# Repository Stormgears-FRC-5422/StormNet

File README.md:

# StormNet
Electrical schematics and other files related to the StormNet sensor board

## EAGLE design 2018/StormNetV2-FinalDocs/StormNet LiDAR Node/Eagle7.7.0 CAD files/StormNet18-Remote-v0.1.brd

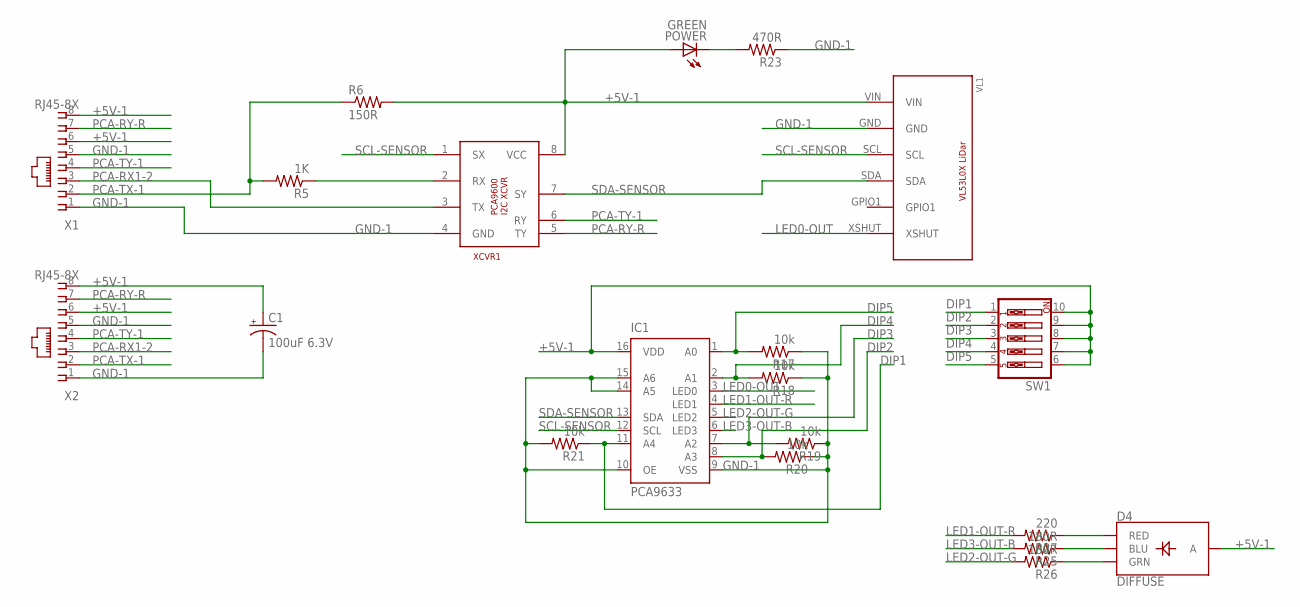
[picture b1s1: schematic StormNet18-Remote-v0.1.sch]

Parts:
C1: 100uF 6.3V; CT3528
D4: DIFFUSE; LED-RGB-THRU
IC1: PCA9633; SO16
POWER: GREEN; CHIPLED_1206
R5: 1K; R0603
R6: 150R; R0603
R17, R18, R19, R20, R21: 10k; R0603
R23: 470R; R0603
R25, R26: 180R; R0603
R27: 220; R0603
SW1: SW_DIP-5; EDG-05
VL1: VL53L0X-GREEN
X1, X2: RJ45-8X; RJ45-NO-SHIELD
XCVR1: PCA9600DSO8; SO08

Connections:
+5V-1: C1.+, D4.2 (A), IC1.16 (VDD), POWER.A, R6.2, SW1.6, SW1.7, SW1.8, SW1.9, SW1.10, VL1.VIN, X1.6, X1.8, X2.6, X2.8, XCVR1.8 (VCC)
BLUE: D4.4 (BLU), R25.1
DIP1: IC1.11 (A4), R21.1, SW1.1
DIP2: IC1.8 (A3), R20.2, SW1.2
DIP3: IC1.7 (A2), R19.2, SW1.3
DIP4: IC1.2 (A1), R18.2, SW1.4
DIP5: IC1.1 (A0), R17.2, SW1.5
GND-1: C1.-, IC1.9 (VSS), IC1.10 (OE), IC1.14 (A5), IC1.15 (A6), R17.1, R18.1, R19.1, R20.1, R21.2, R23.1, VL1.GND, X1.1, X1.5, X2.1, X2.5, XCVR1.4 (GND)
GREEN: D4.3 (GRN), R26.1
LED0-OUT: IC1.3 (LED0), VL1.XSHUT
LED1-OUT-R: IC1.4 (LED1), R27.2
LED2-OUT-G: IC1.5 (LED2), R26.2
LED3-OUT-B: IC1.6 (LED3), R25.2
unnamed: R5.1, XCVR1.2 (RX)
unnamed: POWER.C, R23.2
PCA-RX1-2: X1.3, X2.3, XCVR1.3 (TX)
PCA-RY-R: X1.7, X2.7, XCVR1.5 (TY)
PCA-TX-1: R5.2, R6.1, X1.2, X2.2
PCA-TY-1: X1.4, X2.4, XCVR1.6 (RY)
RED: D4.1 (RED), R27.1
SCL-SENSOR: IC1.12 (SCL), VL1.SCL, XCVR1.1 (SX)
SDA-SENSOR: IC1.13 (SDA), VL1.SDA, XCVR1.7 (SY)

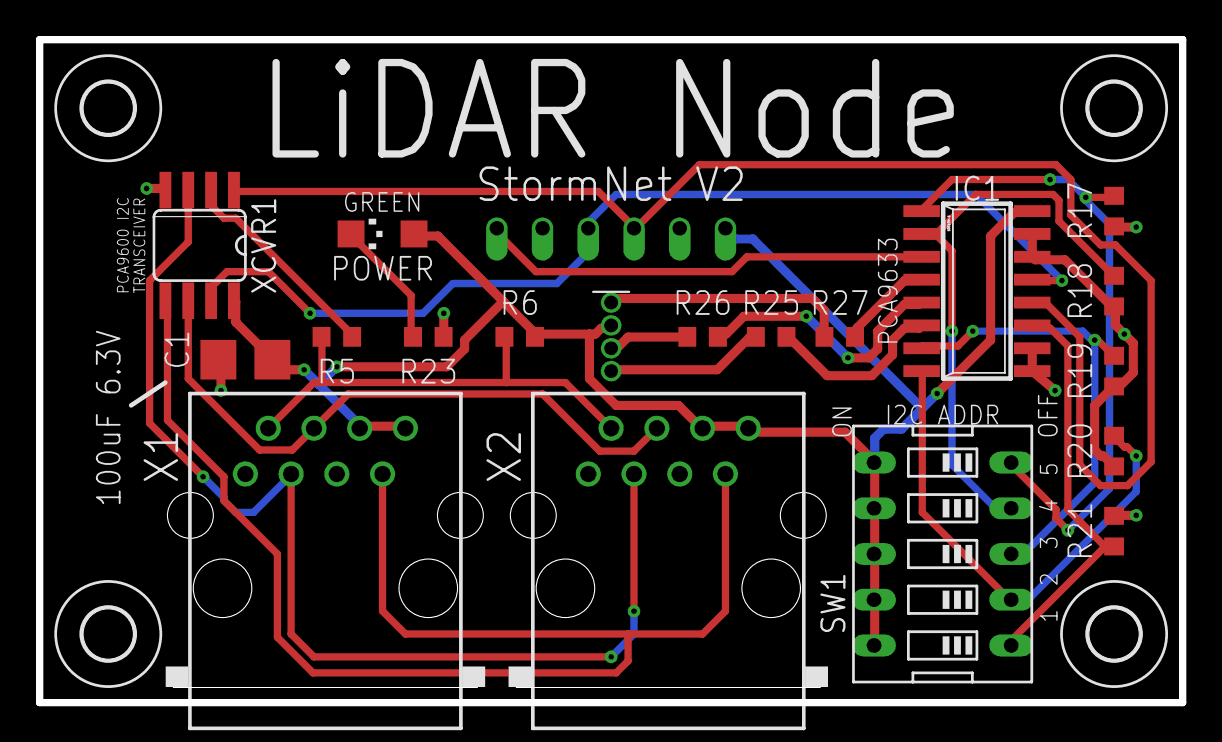
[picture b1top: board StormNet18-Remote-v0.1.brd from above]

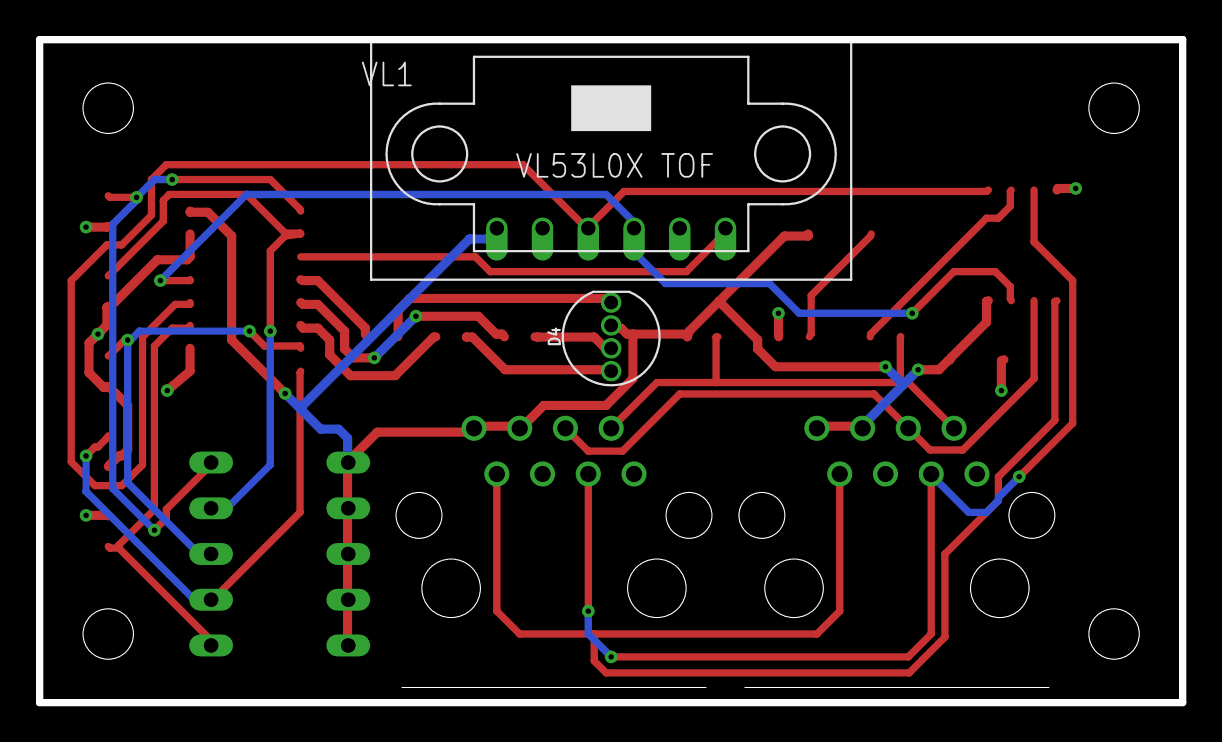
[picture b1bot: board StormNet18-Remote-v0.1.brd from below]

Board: 2 copper layers, 63.5 x 36.8 mm, 24 parts (2 on the bottom side), 22 nets.

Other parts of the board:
U$5, U$6, U$7, U$8: 2,8

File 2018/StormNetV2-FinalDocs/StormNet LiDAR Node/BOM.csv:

"Part","Value","Device","Package","DescriptionMF","MPN","OC_FARNELL","OC_NEWARK","PROD_ID","VALUE",
"C1","100uF 6.3V","CPOL-USCT3528","CT3528","POLARIZED CAPACITOR, American symbol","","","","","",
"D4","DIFFUSE","LED-RGB-CADIFFUSE","LED-RGB-THRU","LED-RGB Diffused Common Anode","","","","","DIO-10632",
"IC1","PCA9633","PCA9633","SO16","4-bit I2C-bus and SMBus low power I/O port with LED drivers","","","","","",
"POWER","GREEN","LEDCHIPLED_1206","CHIPLED_1206","LED","","","","","",
"R5","1K","R-US_R0603","R0603","RESISTOR, American symbol","","","","","",
"R6","150R","R-US_R0603","R0603","RESISTOR, American symbol","","","","","",
"R17","10k","R-US_R0603","R0603","RESISTOR, American symbol","","","","","",
"R18","10k","R-US_R0603","R0603","RESISTOR, American symbol","","","","","",
"R19","10k","R-US_R0603","R0603","RESISTOR, American symbol","","","","","",
"R20","10k","R-US_R0603","R0603","RESISTOR, American symbol","","","","","",
"R21","10k","R-US_R0603","R0603","RESISTOR, American symbol","","","","","",
"R23","470R","R-US_R0603","R0603","RESISTOR, American symbol","","","","","",
"R25","180R","R-US_R0603","R0603","RESISTOR, American symbol","","","","","",
"R26","180R","R-US_R0603","R0603","RESISTOR, American symbol","","","","","",
"R27","220","R-US_R0603","R0603","RESISTOR, American symbol","","","","","",
"SW1","","SW_DIP-5","EDG-05","DIP SWITCH","","","","","",
"VL1","VL53L0X-GREEN","VL53L0X-GREEN","VL53L0X-GREEN","","","","","","",
"X1","RJ45-8X","RJ45-8X","RJ45-NO-SHIELD","CORCOM Modular RJ Jacks No Shield","","RJ45-8X","unknown","16R6101","",
"X2","RJ45-8X","RJ45-8X","RJ45-NO-SHIELD","CORCOM Modular RJ Jacks No Shield","","RJ45-8X","unknown","16R6101","",
"XCVR1","PCA9600DSO8","PCA9600DSO8","SO08","NXP PCA9600 I2C long distance driver","","","","","",

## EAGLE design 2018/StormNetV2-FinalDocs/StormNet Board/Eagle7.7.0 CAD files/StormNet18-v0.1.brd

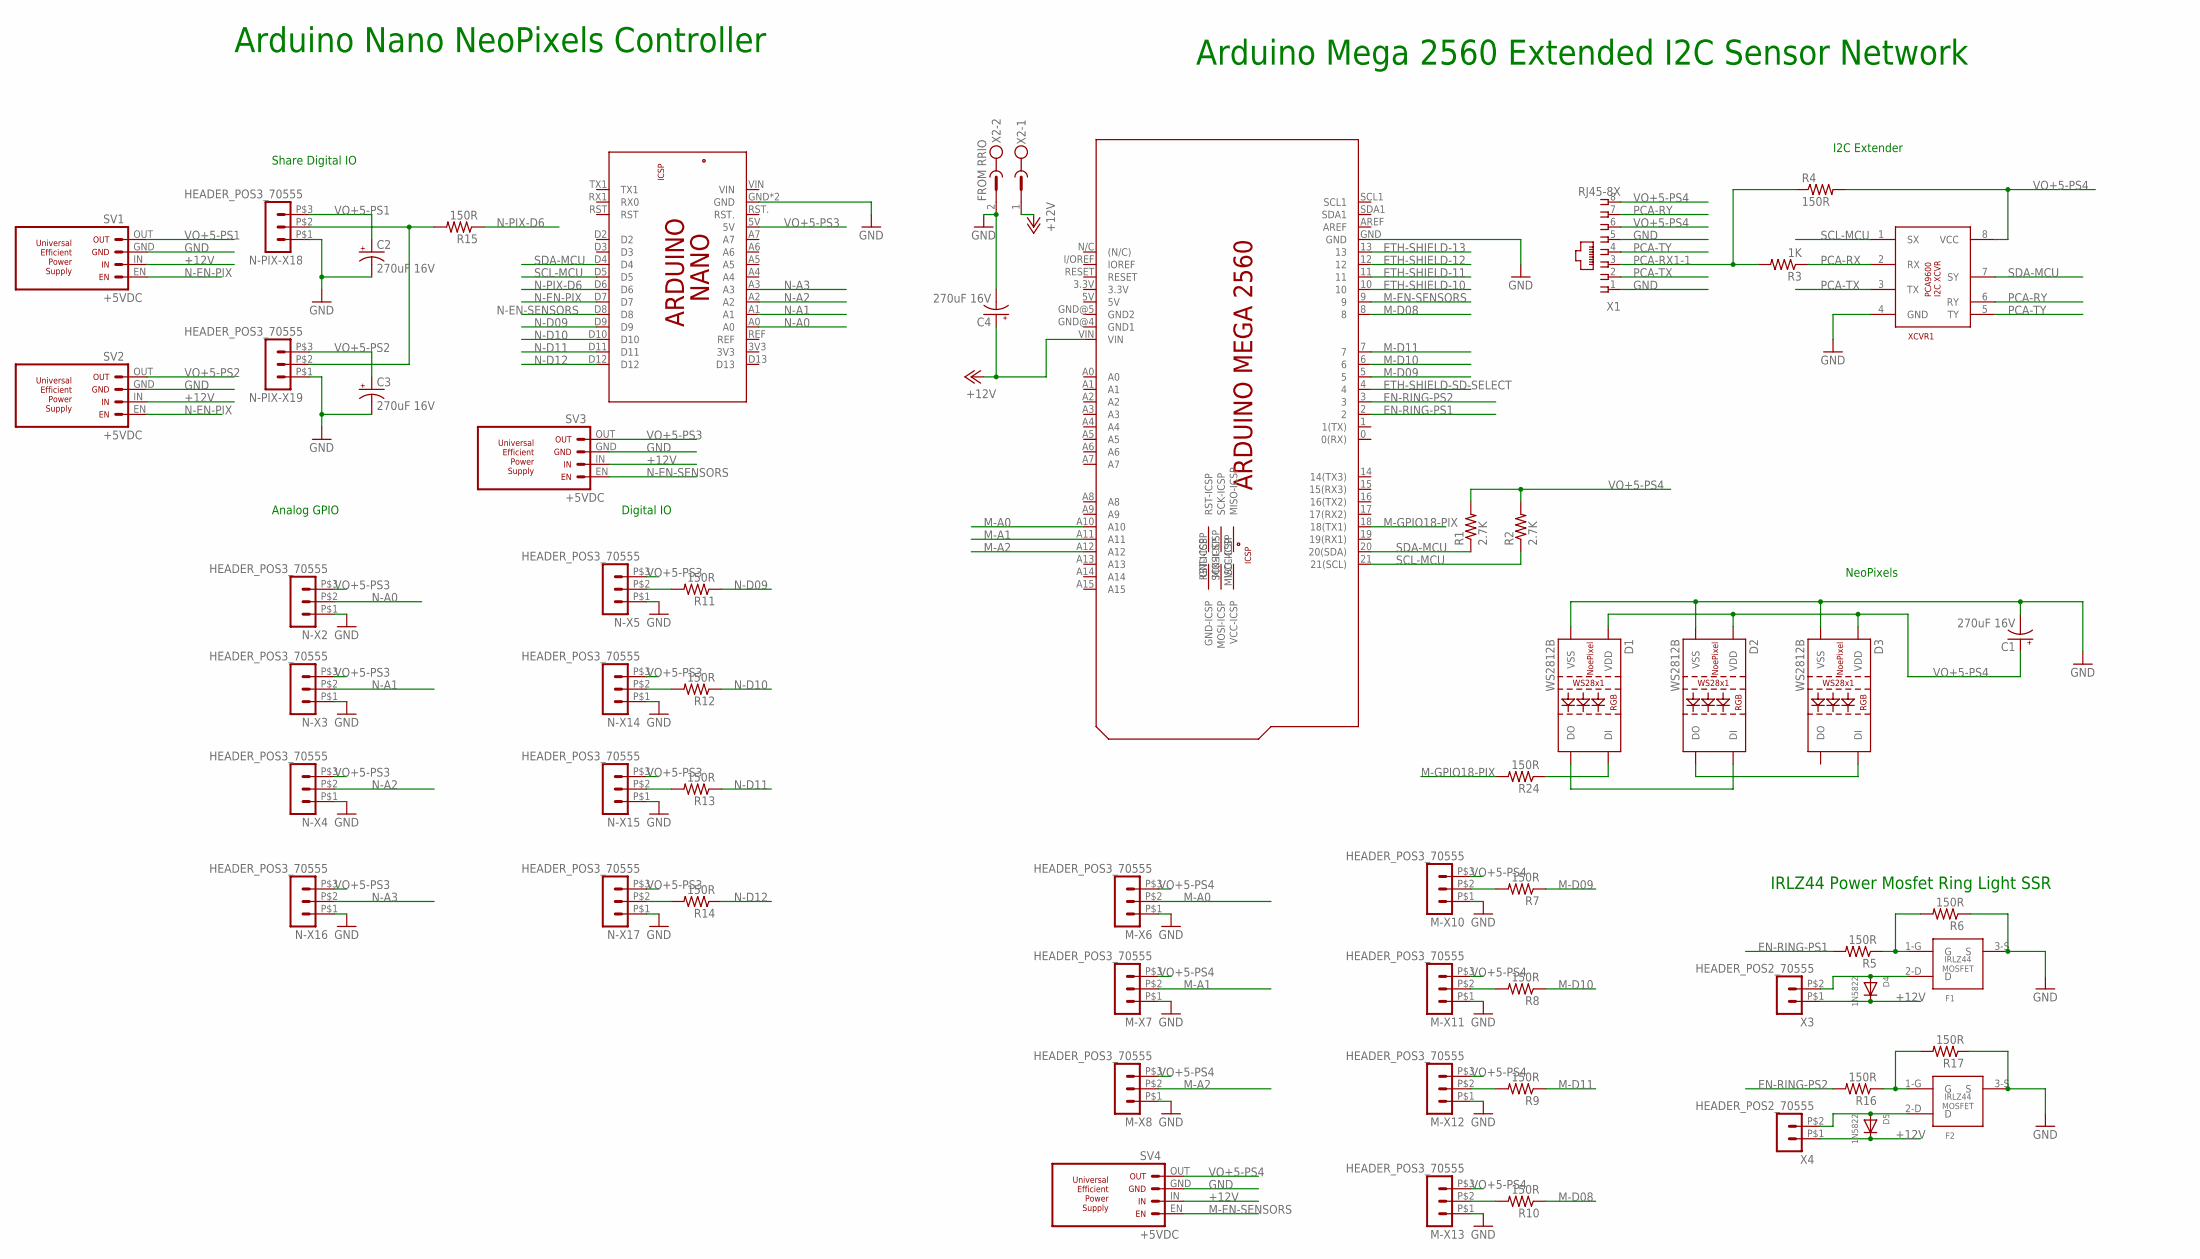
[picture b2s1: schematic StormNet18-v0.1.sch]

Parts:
C1, C2, C3, C4: 270uF 16V; E3,5-8
D1, D2, D3: WS2812B
D4, D5: 1N5822; SMADIODE
F1, F2: IRLZ44; IRLZ44-TO220
M-X6, M-X7, M-X8, M-X10, M-X11, M-X12, M-X13: HEADER_POS3_70555; 70555-POS3
N-PIX-X18, N-PIX-X19: HEADER_POS3_70555; 70555-POS3
N-X2, N-X3, N-X4, N-X5, N-X14, N-X15, N-X16, N-X17: HEADER_POS3_70555; 70555-POS3
PCB2: ARDUINO_MEGA2560_SMALL
PCB3: ARDUINO_NANOWITHOUT_ICSP; ARDUINO_NANO
R1, R2: 2.7K; R0603
R3: 1K; R0603
R4, R5, R6, R7, R8, R9, R10, R11, R12, R13, R14, R15, R16, R17, R24: 150R; R0603
SV1, SV2, SV3, SV4: +5VDC; PS-UNIV-EFFICIENT-3A
X1: RJ45-8X; RJ45-NO-SHIELD
X2: FROM RRIO; MSTBV2-SMALL
X3, X4: HEADER_POS2_70555; 70555-POS2
XCVR1: PCA9600DSO8; SO08

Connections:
3.3V: PCB2.3.3V
5V: PCB2.5V
+12V: C4.+, D4.C, D5.C, PCB2.VIN, SV1.IN, SV2.IN, SV3.IN, SV4.IN, X2.1, X3.P$1 (1), X4.P$1 (1)
EN-RING-PS1: PCB2.2, R5.2
EN-RING-PS2: PCB2.3, R16.2
ETH-SHIELD-10: PCB2.10
ETH-SHIELD-11: PCB2.11
ETH-SHIELD-12: PCB2.12
ETH-SHIELD-13: PCB2.13
ETH-SHIELD-SD-SELECT: PCB2.4
GND: C1.-, C2.-, C3.-, C4.-, D1.3 (VSS), D2.3 (VSS), D3.3 (VSS), F1.3-S (S), F2.3-S (S), M-X6.P$1 (1), M-X7.P$1 (1), M-X8.P$1 (1), M-X10.P$1 (1), M-X11.P$1 (1), M-X12.P$1 (1), M-X13.P$1 (1), N-PIX-X18.P$1 (1), N-PIX-X19.P$1 (1), N-X2.P$1 (1), N-X3.P$1 (1), N-X4.P$1 (1), N-X5.P$1 (1), N-X14.P$1 (1), N-X15.P$1 (1), N-X16.P$1 (1), N-X17.P$1 (1), PCB2.GND, PCB3.GND, PCB3.GND@1 (GND), R6.1, R17.1, SV1.GND, SV2.GND, SV3.GND, SV4.GND, X1.1, X1.5, X2.2, XCVR1.4 (GND)
GND1: PCB2.GND@4 (GND1)
GND2: PCB2.GND@5 (GND2)
M-A0: M-X6.P$2 (2), PCB2.A10
M-A1: M-X7.P$2 (2), PCB2.A11
M-A2: M-X8.P$2 (2), PCB2.A12
M-D08: PCB2.8, R10.1
M-D09: PCB2.5, R7.1
M-D10: PCB2.6, R8.1
M-D11: PCB2.7, R9.1
M-EN-SENSORS: PCB2.9, SV4.EN
M-GPIO18-PIX: PCB2.18 (18(TX1)), R24.2
unnamed: M-X10.P$2 (2), R7.2
unnamed: N-PIX-X18.P$2 (2), N-PIX-X19.P$2 (2), R15.2
unnamed: M-X11.P$2 (2), R8.2
unnamed: M-X12.P$2 (2), R9.2
unnamed: M-X13.P$2 (2), R10.2
unnamed: F1.1-G (G), R5.1, R6.2
unnamed: D4.A, F1.2-D (D), X3.P$2 (2)
unnamed: N-X5.P$2 (2), R11.2
unnamed: N-X14.P$2 (2), R12.2
unnamed: N-X15.P$2 (2), R13.2
unnamed: N-X17.P$2 (2), R14.2
unnamed: F2.1-G (G), R16.1, R17.2
unnamed: D5.A, F2.2-D (D), X4.P$2 (2)
unnamed: D1.4 (DI), R24.1
unnamed: D2.2 (DO), D3.4 (DI)
unnamed: D1.2 (DO), D2.4 (DI)
N-A0: N-X2.P$2 (2), PCB3.A0
N-A1: N-X3.P$2 (2), PCB3.A1
N-A2: N-X4.P$2 (2), PCB3.A2
N-A3: N-X16.P$2 (2), PCB3.A3
N-D09: PCB3.D9, R11.1
N-D10: PCB3.D10, R12.1
N-D11: PCB3.D11, R13.1
N-D12: PCB3.D12, R14.1
N-EN-PIX: PCB3.D7, SV1.EN, SV2.EN
N-EN-SENSORS: PCB3.D8, SV3.EN
N-PIX-D6: PCB3.D6, R15.1
PCA-RX: R3.1, XCVR1.2 (RX)
PCA-RX1-1: R3.2, R4.1, X1.3
PCA-RY: X1.7, XCVR1.6 (RY)
PCA-TX: X1.2, XCVR1.3 (TX)
PCA-TY: X1.4, XCVR1.5 (TY)
SCL-MCU: PCB2.21 (21(SCL)), PCB3.D5, R2.1, XCVR1.1 (SX)
SDA-MCU: PCB2.20 (20(SDA)), PCB3.D4, R1.1, XCVR1.7 (SY)
VO+5-PS1: C2.+, N-PIX-X18.P$3 (3), SV1.OUT
VO+5-PS2: C3.+, N-PIX-X19.P$3 (3), SV2.OUT
VO+5-PS3: N-X2.P$3 (3), N-X3.P$3 (3), N-X4.P$3 (3), N-X5.P$3 (3), N-X14.P$3 (3), N-X15.P$3 (3), N-X16.P$3 (3), N-X17.P$3 (3), PCB3.5V, SV3.OUT
VO+5-PS4: C1.+, D1.1 (VDD), D2.1 (VDD), D3.1 (VDD), M-X6.P$3 (3), M-X7.P$3 (3), M-X8.P$3 (3), M-X10.P$3 (3), M-X11.P$3 (3), M-X12.P$3 (3), M-X13.P$3 (3), R1.2, R2.2, R4.2, SV4.OUT, X1.6, X1.8, XCVR1.8 (VCC)

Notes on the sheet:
Arduino Mega 2560 Extended I2C Sensor Network
Arduino Nano NeoPixels Controller
Share Digital IO
Analog GPIO
Digital IO
NeoPixels
I2C Extender
IRLZ44 Power Mosfet Ring Light SSR

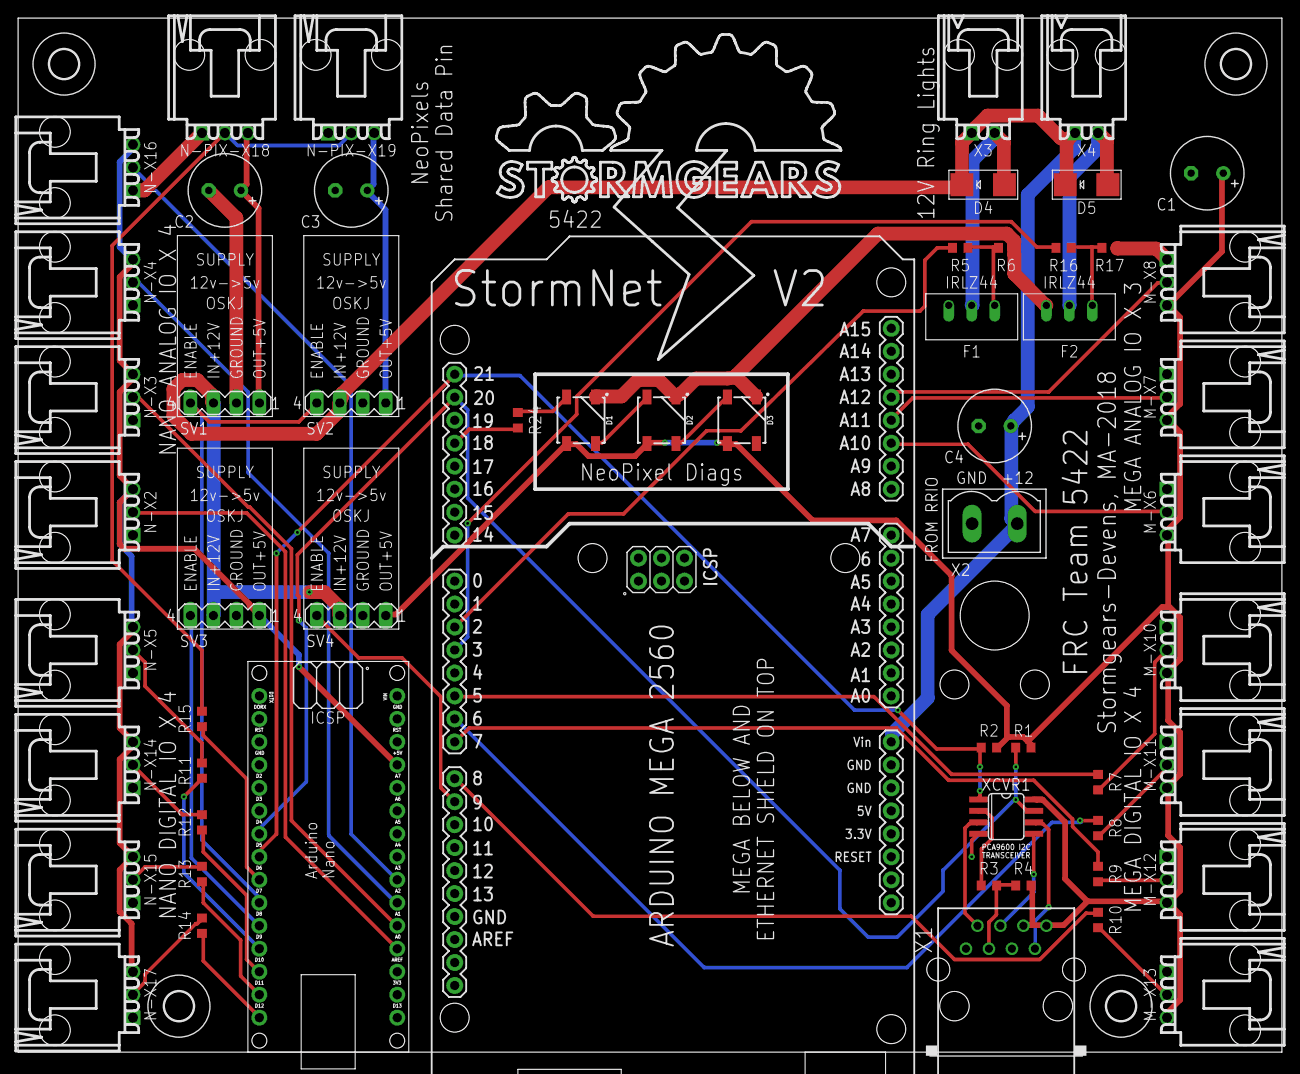
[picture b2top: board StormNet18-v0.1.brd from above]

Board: 2 copper layers, 139.7 x 114.7 mm, 61 parts (0 on the bottom side), 51 nets.

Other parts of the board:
U$1, U$2, U$3, U$4: 3,2

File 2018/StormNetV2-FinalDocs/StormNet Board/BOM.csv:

"Part","Value","Device","Package","DescriptionMF","MPN","OC_FARNELL","OC_NEWARK","PROD_ID","VALUE",
"C1","270uF 16V","CPOL-USE3.5-8","E3,5-8","POLARIZED CAPACITOR, American symbol","","","","","",
"C2","270uF 16V","CPOL-USE3.5-8","E3,5-8","POLARIZED CAPACITOR, American symbol","","","","","",
"C3","270uF 16V","CPOL-USE3.5-8","E3,5-8","POLARIZED CAPACITOR, American symbol","","","","","",
"C4","270uF 16V","CPOL-USE3.5-8","E3,5-8","POLARIZED CAPACITOR, American symbol","","","","","",
"D1","WS2812B","WS2812B","WS2812B","WS2812B SMD addressable RGB LED","","","","","DIO-12503",
"D2","WS2812B","WS2812B","WS2812B","WS2812B SMD addressable RGB LED","","","","","DIO-12503",
"D3","WS2812B","WS2812B","WS2812B","WS2812B SMD addressable RGB LED","","","","","DIO-12503",
"D4","1N5822","DIODESMA","SMADIODE","Diode","","","","","",
"D5","1N5822","DIODESMA","SMADIODE","Diode","","","","","",
"F1","IRLZ44","IRLZ44","IRLZ44-TO220","","","","","","",
"F2","IRLZ44","IRLZ44","IRLZ44-TO220","","","","","","",
"M-X6","HEADER_POS3_70555","HEADER_POS3_70555","70555-POS3","Molex -C-Grid® / SL Series connector","","","","","",
"M-X7","HEADER_POS3_70555","HEADER_POS3_70555","70555-POS3","Molex -C-Grid® / SL Series connector","","","","","",
"M-X8","HEADER_POS3_70555","HEADER_POS3_70555","70555-POS3","Molex -C-Grid® / SL Series connector","","","","","",
"M-X10","HEADER_POS3_70555","HEADER_POS3_70555","70555-POS3","Molex -C-Grid® / SL Series connector","","","","","",
"M-X11","HEADER_POS3_70555","HEADER_POS3_70555","70555-POS3","Molex -C-Grid® / SL Series connector","","","","","",
"M-X12","HEADER_POS3_70555","HEADER_POS3_70555","70555-POS3","Molex -C-Grid® / SL Series connector","","","","","",
"M-X13","HEADER_POS3_70555","HEADER_POS3_70555","70555-POS3","Molex -C-Grid® / SL Series connector","","","","","",
"N-PIX-X18","HEADER_POS3_70555","HEADER_POS3_70555","70555-POS3","Molex -C-Grid® / SL Series connector","","","","","",
"N-PIX-X19","HEADER_POS3_70555","HEADER_POS3_70555","70555-POS3","Molex -C-Grid® / SL Series connector","","","","","",
"N-X2","HEADER_POS3_70555","HEADER_POS3_70555","70555-POS3","Molex -C-Grid® / SL Series connector","","","","","",
"N-X3","HEADER_POS3_70555","HEADER_POS3_70555","70555-POS3","Molex -C-Grid® / SL Series connector","","","","","",
"N-X4","HEADER_POS3_70555","HEADER_POS3_70555","70555-POS3","Molex -C-Grid® / SL Series connector","","","","","",
"N-X5","HEADER_POS3_70555","HEADER_POS3_70555","70555-POS3","Molex -C-Grid® / SL Series connector","","","","","",
"N-X14","HEADER_POS3_70555","HEADER_POS3_70555","70555-POS3","Molex -C-Grid® / SL Series connector","","","","","",
"N-X15","HEADER_POS3_70555","HEADER_POS3_70555","70555-POS3","Molex -C-Grid® / SL Series connector","","","","","",
"N-X16","HEADER_POS3_70555","HEADER_POS3_70555","70555-POS3","Molex -C-Grid® / SL Series connector","","","","","",
"N-X17","HEADER_POS3_70555","HEADER_POS3_70555","70555-POS3","Molex -C-Grid® / SL Series connector","","","","","",
"PCB2","ARDUINO_MEGA2560_SMALL","ARDUINO_MEGA2560_SMALL","ARDUINO_MEGA2560_SMALL","Device for representing an Arduino Mega 2560 board with a footprint in an EAGLE design. Created by Dave Young for Element14. More EAGLE documentation at: http://www.element14.com/community/community/knode/cadsoft_eagle","","","","","",
"PCB3","ARDUINO_NANOWITHOUT_ICSP","ARDUINO_NANOWITHOUT_ICSP","ARDUINO_NANO","Device for representing an Arduino Nano board with a footprint in an EAGLE design. Created by Dave Young for Element14. More EAGLE documentation at: http://www.element14.com/community/community/knode/cadsoft_eagle","","","","","",
"R1","2.7K","R-US_R0603","R0603","RESISTOR, American symbol","","","","","",
"R2","2.7K","R-US_R0603","R0603","RESISTOR, American symbol","","","","","",
"R3","1K","R-US_R0603","R0603","RESISTOR, American symbol","","","","","",
"R4","150R","R-US_R0603","R0603","RESISTOR, American symbol","","","","","",
"R5","150R","R-US_R0603","R0603","RESISTOR, American symbol","","","","","",
"R6","150R","R-US_R0603","R0603","RESISTOR, American symbol","","","","","",
"R7","150R","R-US_R0603","R0603","RESISTOR, American symbol","","","","","",
"R8","150R","R-US_R0603","R0603","RESISTOR, American symbol","","","","","",
"R9","150R","R-US_R0603","R0603","RESISTOR, American symbol","","","","","",
"R10","150R","R-US_R0603","R0603","RESISTOR, American symbol","","","","","",
"R11","150R","R-US_R0603","R0603","RESISTOR, American symbol","","","","","",
"R12","150R","R-US_R0603","R0603","RESISTOR, American symbol","","","","","",
"R13","150R","R-US_R0603","R0603","RESISTOR, American symbol","","","","","",
"R14","150R","R-US_R0603","R0603","RESISTOR, American symbol","","","","","",
"R15","150R","R-US_R0603","R0603","RESISTOR, American symbol","","","","","",
"R16","150R","R-US_R0603","R0603","RESISTOR, American symbol","","","","","",
"R17","150R","R-US_R0603","R0603","RESISTOR, American symbol","","","","","",
"R24","150R","R-US_R0603","R0603","RESISTOR, American symbol","","","","","",
"SV1","+5VDC","SUPPLY-UNIV-EFFICIENT","PS-UNIV-EFFICIENT-3A","PIN HEADER","","","unknown","unknown","",
"SV2","+5VDC","SUPPLY-UNIV-EFFICIENT","PS-UNIV-EFFICIENT-3A","PIN HEADER","","","unknown","unknown","",
"SV3","+5VDC","SUPPLY-UNIV-EFFICIENT","PS-UNIV-EFFICIENT-3A","PIN HEADER","","","unknown","unknown","",
"SV4","+5VDC","SUPPLY-UNIV-EFFICIENT","PS-UNIV-EFFICIENT-3A","PIN HEADER","","","unknown","unknown","",
"X1","RJ45-8X","RJ45-8X","RJ45-NO-SHIELD","CORCOM Modular RJ Jacks No Shield","","RJ45-8X","unknown","16R6101","",
"X2","FROM RRIO","MSTBV2","MSTBV2-SMALL","PHOENIX","","","","","",
"X3","HEADER_POS2_70555","HEADER_POS2_70555","70555-POS2","Molex -C-Grid® / SL Series connector","","","","","",
"X4","HEADER_POS2_70555","HEADER_POS2_70555","70555-POS2","Molex -C-Grid® / SL Series connector","","","","","",
"XCVR1","PCA9600DSO8","PCA9600DSO8","SO08","NXP PCA9600 I2C long distance driver","","","","","",

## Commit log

2020-01-03 Initial consolidated git reposit of all StormNet versions to date.

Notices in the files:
parts and their libraries:
SparkFun-LED: Licensing: Creative Commons ShareAlike 4.0 International - https://creativecommons.org/licenses/by-sa/4.0
